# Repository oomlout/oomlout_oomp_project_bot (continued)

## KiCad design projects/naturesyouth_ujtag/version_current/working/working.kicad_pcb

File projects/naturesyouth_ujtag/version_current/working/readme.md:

# OOMP Project  
## uJTAG  by naturesyouth  
  
oomp key: oomp_projects_flat_naturesyouth_ujtag  
(snippet of original readme)  

  full source readme at [readme_src.md](readme_src.md)  
  
source repo at: [https://github.com/naturesyouth/uJTAG](https://github.com/naturesyouth/uJTAG)  
## Board  

## Schematic  

[schematic pdf](working_schematic.pdf)  
## Images

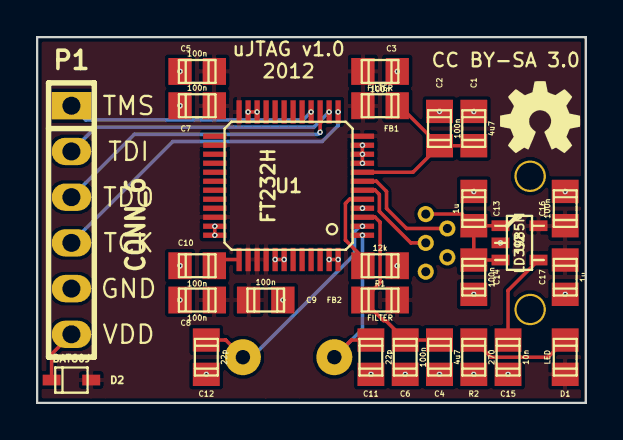
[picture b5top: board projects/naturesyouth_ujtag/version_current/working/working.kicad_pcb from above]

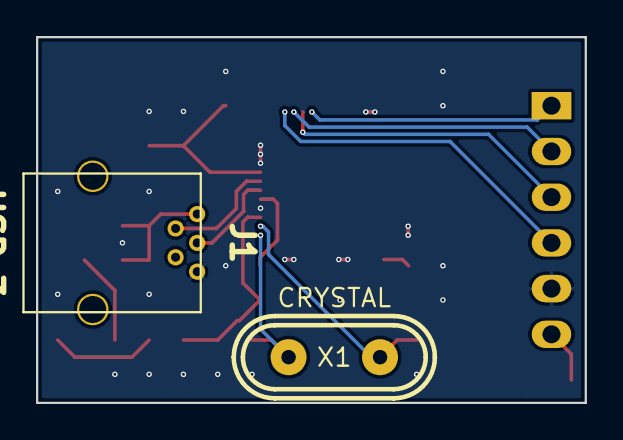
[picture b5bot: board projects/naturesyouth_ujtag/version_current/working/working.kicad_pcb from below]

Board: 2 copper layers, 30.5 x 20.3 mm, 29 parts (2 on the bottom side), 18 nets.

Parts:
C1, C4: 4u7; c_0805
C2, C3, C5, C6, C7, C8, C9, C10, C14, C16: 100n; c_0805
C11, C12: 22p; c_0805
C13, C17: 1u; c_0805
C15: 10n; c_0805
D1: LED; r_0805
D2: BAT60J; sod323
FB1, FB2: FILTER; r_0805
J1: USB_3; conn_usb_mini_th
LOGO1: OPEN_HARDWARE_2; oshw_silkscreen_4
P1: CONN_6; pin_strip_6
R1: 12k; r_0805
R2: 270; r_0805
U1: FT232H; lqfp48
U2: LD3985M; sot23-5
X1: CRYSTAL; hc-49s

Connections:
3V3: C3.2, C5.2, C7.2, C8.1, C9.1, C16.1, C17.1, D1.1, D2.1, FB1.1, FB2.1, U1.12, U1.24, U1.26, U1.34, U1.38, U1.39, U1.40, U2.5
+5V: C13.1, C14.1, J1.1, U2.1, U2.3
/D+: J1.2, U1.7
/D-: J1.3, U1.6
/TCK: P1.4, U1.13
/TDI: P1.2, U1.14
/TDO: P1.3, U1.15
/TMS: P1.1, U1.16
GND: C1.1, C2.1, C3.1, C4.2, C5.1, C6.2, C7.1, C8.2, C9.2, C10.2, C11.2, C12.2, C13.2, C14.2, C15.2, C16.2, C17.2, J1.5, P1.5, R1.2, R2.2, U1.4, U1.9, U1.10, U1.11, U1.22, U1.23, U1.35, U1.36, U1.41, U1.42, U1.47, U1.48, U2.2
unnamed: C4.1, C6.1, FB2.2, U1.3
unnamed: C10.1, U1.37
unnamed: C11.1, U1.1, X1.2
unnamed: R1.1, U1.5
unnamed: C12.1, U1.2, X1.1
unnamed: C1.2, C2.2, FB1.2, U1.8
unnamed: C15.1, U2.4
unnamed: D1.2, R2.1
unnamed: D2.2, P1.6

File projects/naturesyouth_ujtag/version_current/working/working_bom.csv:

"Id";"Designator";"Footprint";"Quantity";"Designation";"Supplier and ref";
1;"U2";"sot23-5";1;"LD3985M";;;
2;"D2";"sod323";1;"BAT60J";;;
3;"R2";"r_0805";1;"270";;;
4;"R1";"r_0805";1;"12k";;;
5;"FB2,FB1";"r_0805";2;"FILTER";;;
6;"D1";"r_0805";1;"LED";;;
7;"P1";"pin_strip_6";1;"CONN_6";;;
8;"J1";"conn_usb_mini_th";1;"USB_3";;;
9;"C15";"c_0805";1;"10n";;;
10;"C17,C13";"c_0805";2;"1u";;;
11;"C16,C14,C10,C9,C8,C7,C6,C5,C3,C2";"c_0805";10;"100n";;;
12;"C1,C4";"c_0805";2;"4u7";;;
13;"C12,C11";"c_0805";2;"22p";;;
14;"X1";"hc-49s";1;"CRYSTAL";;;
15;"LOGO1";"oshw_silkscreen_4";1;"OPEN_HARDWARE_2";;;
16;"U1";"lqfp48";1;"FT232H";;;

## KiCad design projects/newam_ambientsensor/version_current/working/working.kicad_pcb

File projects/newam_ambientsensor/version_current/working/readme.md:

# AmbientSensor by newAM  
This is a harvested standardized copy of a project from github.  
The original project can be found at:  
https://github.com/newAM/AmbientSensor  
Please consult that link for additional, details, files, and license information.  
Note: It was auto harvested and if the original repo had more than one board file or anything out of the ordinary the files here are likely not representative.

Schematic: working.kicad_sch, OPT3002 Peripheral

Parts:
C1: 100u; C_0603
J1: NO; SolderJumper-2_P1.3mm_Open_RoundedPad1.0x1.5mm
J2: NC; SolderJumper-2_P1.3mm_Bridged2Bar_RoundedPad1.0x1.5mm
U1: OPT3002; DFN-6-1EP_2x2mm_Pitch0.65mm; DigiKey Part Number 296-47274-1-ND
X1: RJ22; A-2004-3-4-LP-N-R; DigiKey Part Number AE10381-ND

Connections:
+3V3: C1.1, J1.1 (A), U1.1, X1.4
GND: C1.2, J2.1 (A), U1.3, X1.2
unnamed: J1.2 (B), J2.2 (B), U1.2
SCL: U1.4, X1.1
SDA: U1.6, X1.3

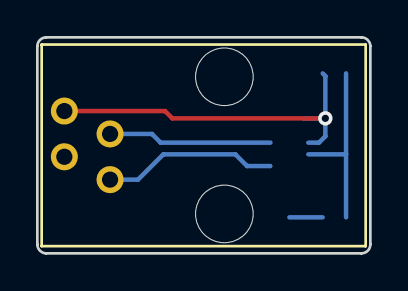
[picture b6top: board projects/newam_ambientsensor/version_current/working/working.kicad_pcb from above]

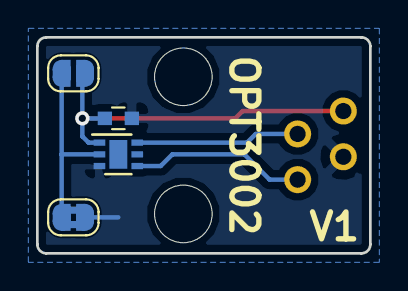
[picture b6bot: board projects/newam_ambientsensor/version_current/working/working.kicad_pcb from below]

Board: 2 copper layers, 18.5 x 12.0 mm, 5 parts (4 on the bottom side), 5 nets.

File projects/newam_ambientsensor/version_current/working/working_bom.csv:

"Id";"Designator";"Footprint";"Quantity";"Designation";"Supplier and ref";
1;"X1";"A-2004-3-4-LP-N-R";1;"RJ22";;;
2;"C1";"C_0603";1;"100u";;;
3;"U1";"DFN-6-1EP_2x2mm_Pitch0.65mm";1;"OPT3002";;;
